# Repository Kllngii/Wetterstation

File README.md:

# Wetterstation

Mit einem WiFi-fähigen Mikrocontroller sollen verschiedene Sensordaten erfasst- und aufbereitet werden. 

Für die WiFi-Anbindung wird ein Raspberry Pi Pico W verwendet, der mit zwei Kernen und einem WLAN/Bluetooth Modul genug Leistung
zur Verfügung stellen kann. 

Die erfassten Daten werden auf einem lokalen (Touch)-Display ausgegeben, durch die WLAN-Fähigkeit könnten die Daten zukünftig auch an eine lokale Datenbank übertragen werden (MySQL/Docker, graphische Aufbereitung mit Grafana o.ä.)

# Sensoren
Folgende Sensoren werden verwendet (das Projekt ist beliebig skalierbar):
## Interne Messgruppe
- BME280 (Temperatur, Luftfeuchtigkeit, Luftdruck)
- MH-Z19C (CO2)
## Externe Messgruppe
- BME280 (Tempertur, Luftfeuchtigkeit, Luftdruck)
- DCF77-Empfänger (Uhrzeit und Wettervorhersage)
    - Der DCF77-Empfänger empfängt das Signal eines Zeitzeichensenders, das neben aktuellen Zeitinformationen eine Wettervorhersage beinhaltet. Diese ist allerdings verschlüsselt. verfügbaren GPIO Pins und Rechenleistung wird die Entschlüsselung auf dem internen Modul vorgenommen. Mit der Nutzung des ESP8266 als Außenmodul ist das ganz sinnvoll, weil der nicht so viele GPIO Pins frei verfügbar hat, ein MSP430 sollte das aber ohne grö0eren Rechenaufwand schaffen. Für die Entschlüsselung der Daten wird ein HKW581 Modul benötigt. 
## Eventuelle Erweiterungen
- DHT22 (Temperatur, Luftfeuchtigkeit)
- PT100/PT1000 (Zwei- oder Vierleitermessung, dazu Konstantstromquelle + rel. hochauflösender ADC (min. 16 bit))
- CCS811 (CO2 und flüchtige organische Verbindungen (TVOC))
- Niederschlagsmessung
- Windgeschwindigkeit und Windrichtung

# Struktur des Repos
- **LaTeX** [Dokumentation des Projekts](#dokumentation)
- **wetterstation-arduinosensor** [Arduino als Sensormodul](#arduino-als-sensormodul)
- **wetterstation-ui/** [Desktop App](#desktop-app)
- **slint-pico/** [Raspberry Pico mit Touchscreen als Interface](#raspberry-pico-mit-touchscreen-als-interface)
- **pcbs/** Hier findet man Schaltpläne und PCBs der Module als [KiCad](https://www.kicad.org) Projekt

# Desktop App

*TODO* Hier müsste man erklären was die Desktop-App ist 

# Dokumentation

Das LaTeX Dokument in diesem Ordner ist die Dokumentation des Projekts.

# Arduino als Sensormodul

Ein kleiner Beispiel-Sketch, der einen Arduino (Uno) benutzt, um die I2C- und Onewire-Sensoren anzusteuern.

# Raspberry Pico mit Touchscreen als Interface 

*TODO* Hier müsste man erklären was die Raspberry-Pi-Pico-App ist

# Aktivität

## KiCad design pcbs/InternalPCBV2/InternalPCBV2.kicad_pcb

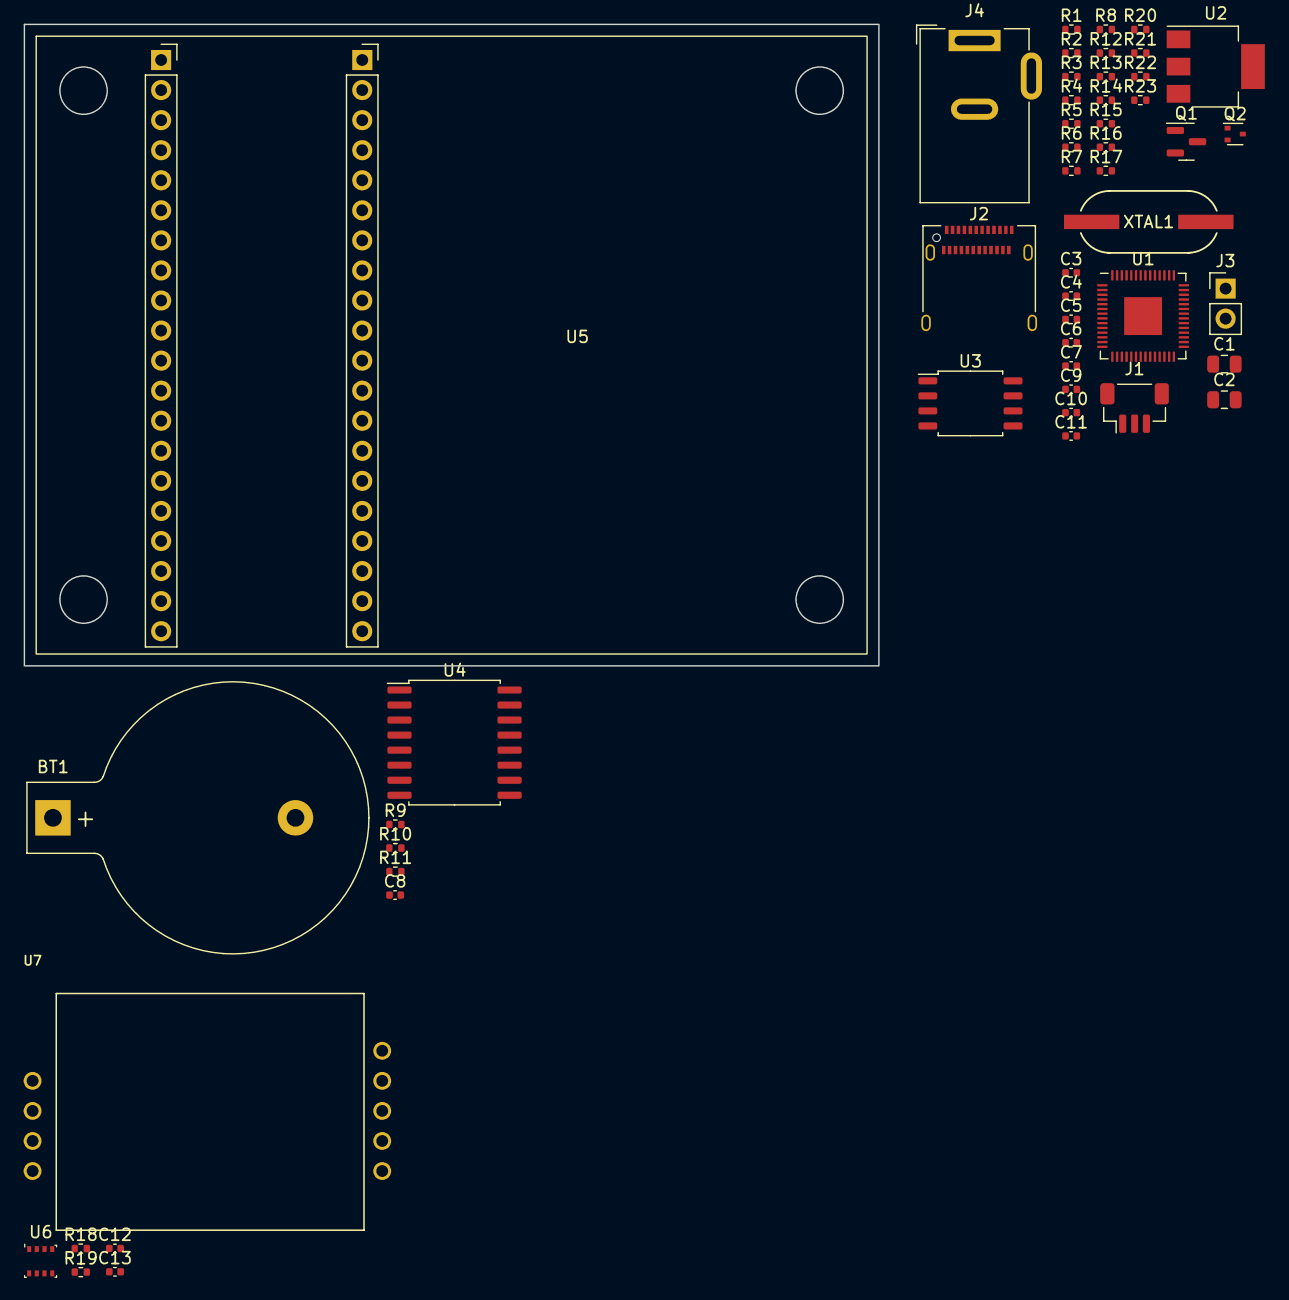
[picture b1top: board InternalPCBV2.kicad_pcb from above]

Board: 2 copper layers, 72.2 x 54.2 mm, 51 parts (0 on the bottom side), 42 nets, no tracks yet.

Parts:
BT1: Battery; BatteryHolder_Keystone_103_1x20mm
C1, C2: 10u; C_0805_2012Metric
C3, C7, C10, C12: 100n; C_0402_1005Metric
C4, C5: 27p; C_0402_1005Metric
C6, C9, C13: 1u; C_0402_1005Metric
C8: 0.1u; C_0402_1005Metric
C11: 1n; C_0402_1005Metric
J1: JST-SH 1x3 SWD Debug; JST_SH_BM03B-SRSS-TB_1x03-1MP_P1.00mm_Vertical
J2: USB_C_Receptacle; USB_C_Receptacle_Amphenol_12401610E4-2A
J3: USB Boot Switch; PinHeader_1x02_P2.54mm_Vertical
J4: 694106301002; BarrelJack_Wuerth_6941xx301002
Q1: DMG2305UX; SOT-23
Q2: DMG1012T; SOT-523
R1, R2: 5.1k; R_0402_1005Metric
R3, R4: 1k; R_0402_1005Metric
R5, R6: 27; R_0402_1005Metric
R7: 100k; R_0402_1005Metric
R8: 200k; R_0402_1005Metric
R9, R10, R11, R18, R19: 10k; R_0402_1005Metric
R12, R13, R14, R15, R16, R17, R20, R21, R22, R23: 0; R_0402_1005Metric
U1: RP2040; QFN-56-1EP_7x7mm_P0.4mm_EP3.2x3.2mm
U2: NCP1117-3.3_SOT223; SOT-223-3_TabPin2
U3: W25Q128JVS; SOIC-8_5.23x5.23mm_P1.27mm
U4: DS3231M; SOIC-16W_7.5x10.3mm_P1.27mm
U5: Pico-ResTouch-LCD-2.8
U6: BME280; Bosch_LGA-8_2.5x2.5mm_P0.65mm_ClockwisePinNumbering
U7: MH-Z19B
XTAL1: ABLS-12.000MHZ-B2-T; XTAL_HC&slash_49US_ABLS_ABR

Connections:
+1V1: C6.1, C7.2, U1.23 (DVDD), U1.45 (VREG_VOUT), U1.50 (DVDD)
+3.3V: C2.1, C3.1, C8.1, C9.1, C10.1, Q2.1 (G), R9.1, R10.1, R11.1, U1.1 (IOVDD), U1.10 (IOVDD), U1.22 (IOVDD), U1.33 (IOVDD), U1.42 (IOVDD), U1.43 (ADC_AVDD), U1.44 (VREG_IN), U1.48 (USB_VDD), U1.49 (IOVDD), U2.2 (VO), U3.8 (VCC), U4.2 (VCC)
+3V3: C12.2, C13.1, R18.1, R19.1, U6.2 (CSB), U6.6 (VDDIO), U6.8 (VDD)
+5V: C1.1, Q1.2 (S), R8.2, U2.3 (VI), U7.VIN
/DEBUG_SC: J1.1, U1.24 (SWCLK)
/DEBUG_SD: J1.3, U1.25 (SWD)
/Display-RTC/I2C0_SCL: R9.2, U4.16 (SCL)
/Display-RTC/I2C0_SDA: R10.2, U4.15 (SDA)
/Display-RTC/RTC_IRQ: R11.2, U4.3 (~INT/SQW)
/FLASH_CLK: U1.52 (QSPI_SCLK), U3.6 (CLK)
/FLASH_CS: R3.2, U1.56 (QSPI_SS), U3.1 (~CS)
/FLASH_SD0: U1.53 (QSPI_SD0), U3.5 (DI(IO0))
/FLASH_SD1: U1.55 (QSPI_SD1), U3.2 (DO(IO1))
/FLASH_SD2: U1.54 (QSPI_SD2), U3.3 (IO2)
/FLASH_SD3: U1.51 (QSPI_SD3), U3.7 (IO3)
/GPIO_0: R22.1, U1.2 (GPIO0)
/GPIO_1: R23.1, U1.3 (GPIO1)
/GPIO_5: R12.1, U1.7 (GPIO5)
/GPIO_18: R13.1, U1.29 (GPIO18)
/GPIO_19: R14.1, U1.30 (GPIO19)
/GPIO_20: R15.1, R20.1
/GPIO_21: R16.1, R21.1
/I2C0_SCL: R21.2, R23.2
/I2C0_SDA: R20.2, R22.2
/Sensors/I2C1_SCL: R18.2, U6.4 (SCK)
/Sensors/I2C1_SDA: R19.2, U6.3 (SDI)
/USB_D+: J2.A6 (D+), J2.B6 (D+), R5.2
/USB_D-: J2.A7 (D-), J2.B7 (D-), R6.1
/VSYS_SENSE: Q2.2 (S), U1.41 (GPIO29_ADC3)
/XIN: C4.2, U1.20 (XIN), XTAL1.1
/XOUT: R4.2, U1.21 (XOUT)
GND: BT1.2 (-), C1.2, C2.2, C3.2, C4.1, C5.1, C6.2, C7.1, C8.2, C9.2, C10.2, C11.1, C12.1, C13.2, J1.2, J2.A1 (GND), J2.A12 (GND), J2.B1 (GND), J2.B12 (GND), J2.S1 (SHIELD), J3.2, J4.2 (GND_1), J4.3 (GND_2), R1.2, R2.2, R7.1, U1.19 (TESTEN), U1.57 (GND), U2.1 (GND), U3.4 (GND), U4.5 (GND), U4.6 (GND), U4.7 (GND), U4.8 (GND), U4.9 (GND), U4.10 (GND), U4.11 (GND), U4.12 (GND), U4.13 (GND), U5.3 (GND), U6.1 (GND), U6.5 (SDO), U6.7 (GND), U7.GND
unnamed: BT1.1 (+), U4.14 (VBAT)
unnamed: C5.2, R4.1, XTAL1.2
unnamed: J2.A5 (CC1), R1.1
unnamed: J2.B5 (CC2), R2.1
unnamed: J3.1, R3.1
unnamed: J4.1 (POWER), Q1.3 (D)
unnamed: C11.2, Q2.3 (D), R7.2, R8.1
unnamed: R6.2, U1.46 (USB_DM)
unnamed: R5.1, U1.47 (USB_DP)
VBUS: J2.A4 (VBUS), J2.A9 (VBUS), J2.B4 (VBUS), J2.B9 (VBUS), Q1.1 (G)

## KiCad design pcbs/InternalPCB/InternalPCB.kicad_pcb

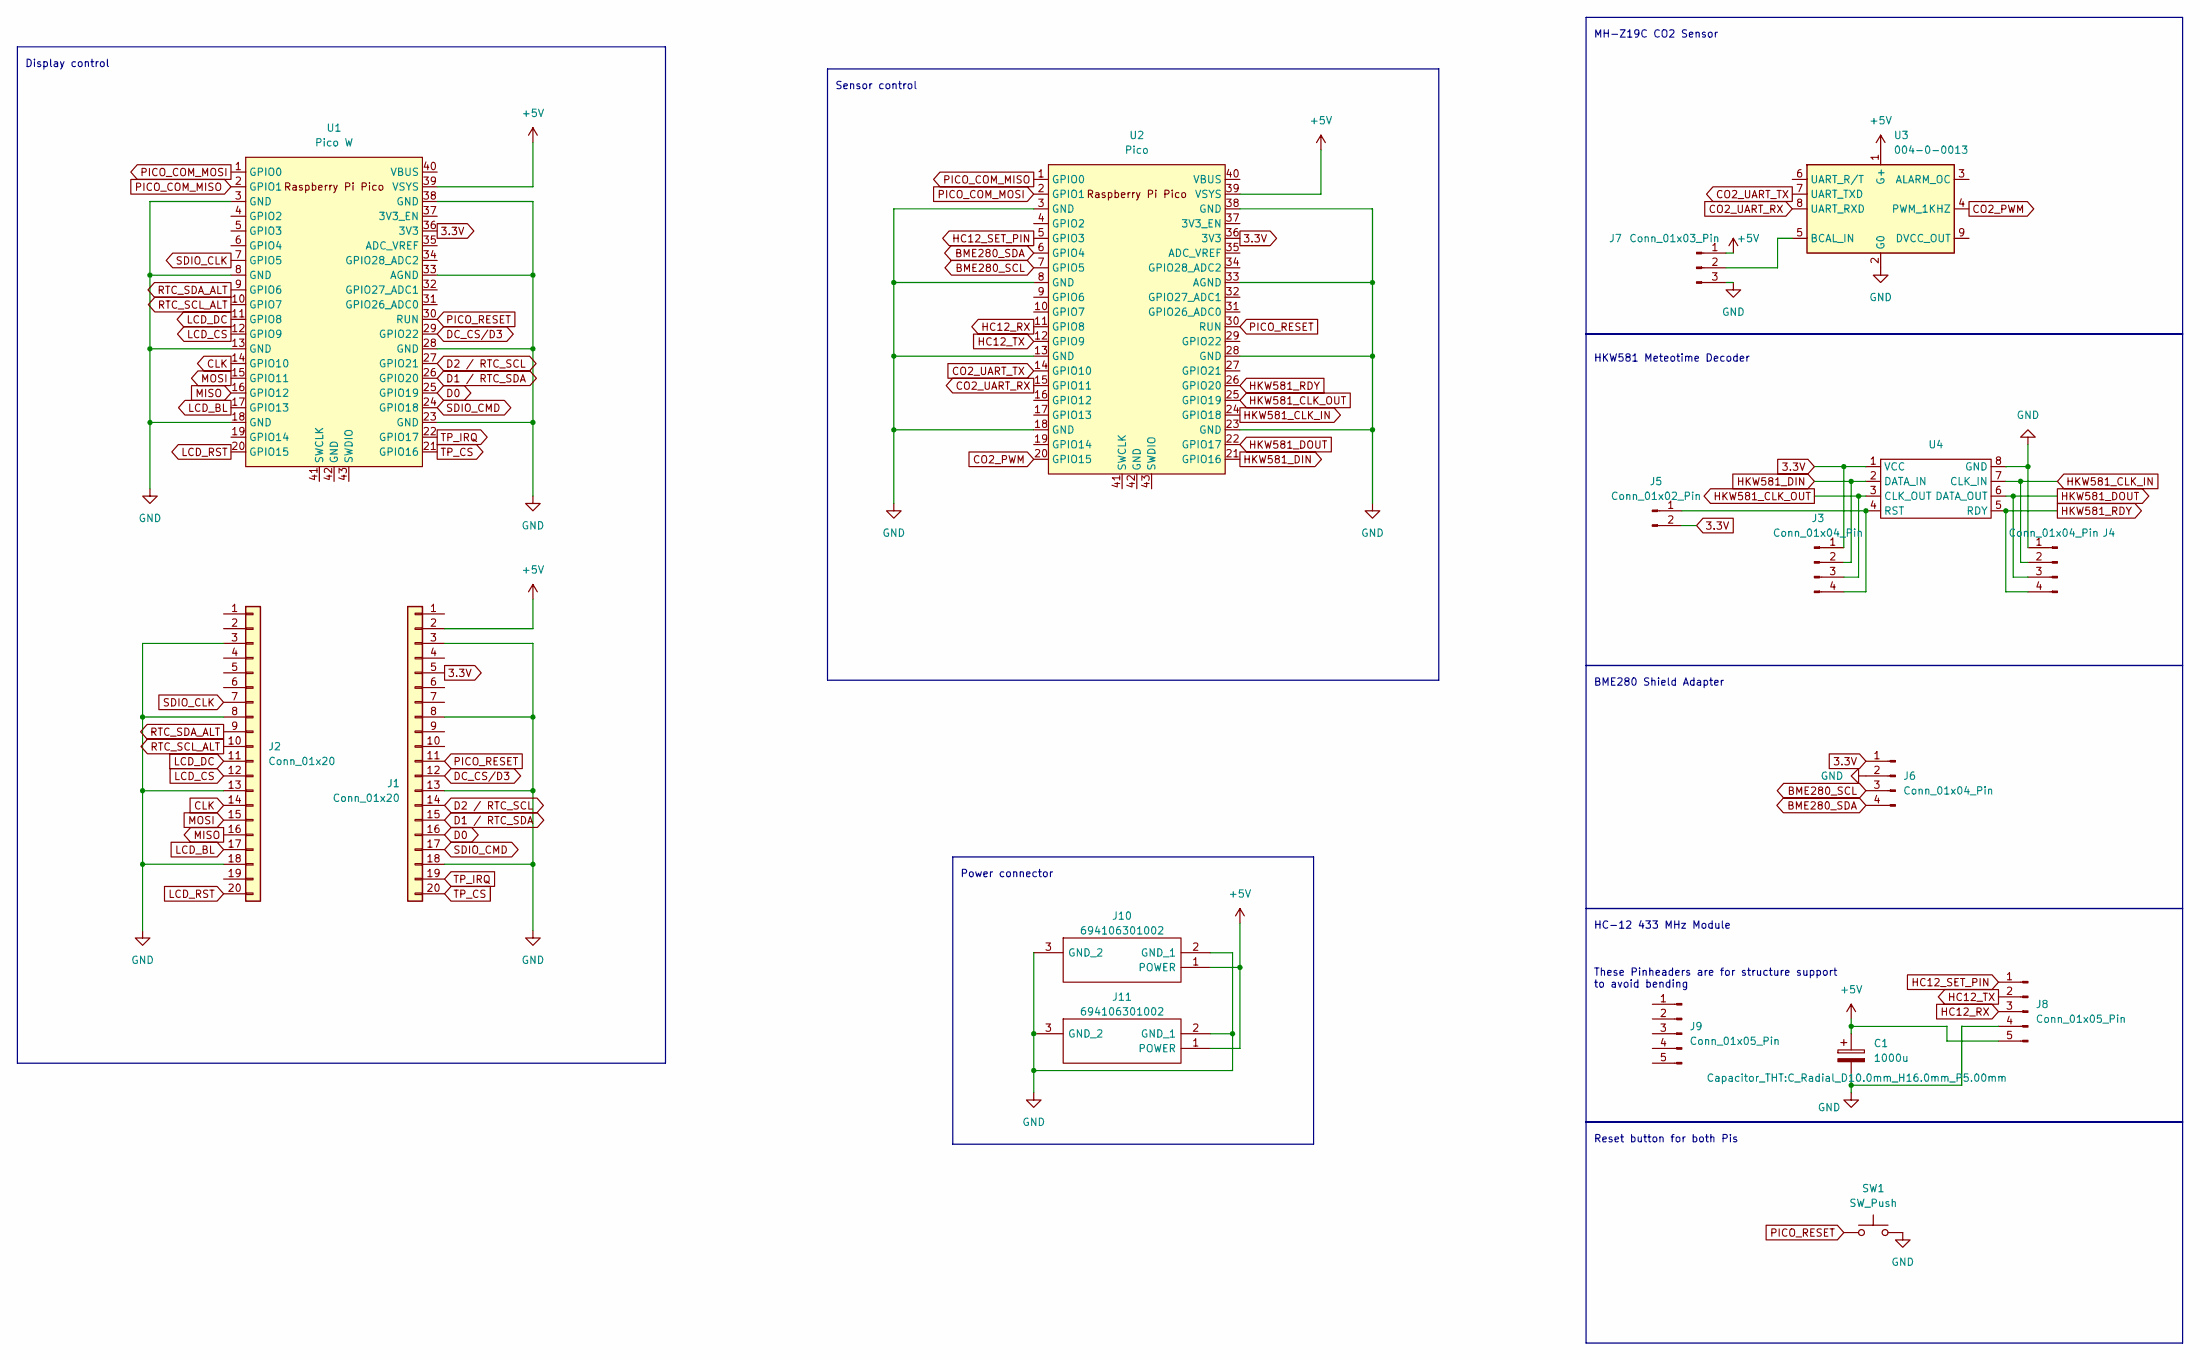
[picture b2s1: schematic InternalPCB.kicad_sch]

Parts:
C1: 1000u; C_Radial_D10.0mm_H16.0mm_P5.00mm
J1, J2: Conn_01x20; PinHeader_1x20_P2.54mm_Vertical
J3, J4, J6: Conn_01x04_Pin; PinHeader_1x04_P2.54mm_Vertical
J5: Conn_01x02_Pin; PinHeader_1x02_P2.54mm_Vertical
J7: Conn_01x03_Pin; PinHeader_1x03_P2.54mm_Vertical
J8, J9: Conn_01x05_Pin; PinHeader_1x05_P2.54mm_Vertical
J10, J11: 694106301002; 694106301002_1; Manufacturer_Part_Number 694106301002; Mouser Part Number 710-694106301002
SW1: SW_Push; SW_PUSH_6mm
U1: Pico W; RPi_Pico_SMD_TH
U2: Pico; RPi_Pico_SMD_TH
U3: 004-0-0013; Senseair_S8_Down
U4: MSOP-8_3x3mm_P0.65mm

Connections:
3.3V: J1.5, J3.1, J5.2, J6.1, U1.36 (3V3), U2.36 (3V3), U4.1 (VCC)
+5V: C1.1, J1.2, J7.1, J8.5, J10.1 (POWER), J11.1 (POWER), U1.39 (VSYS), U2.39 (VSYS), U3.1 (G+)
BME280_SCL: J6.3, U2.7 (GPIO5)
BME280_SDA: J6.4, U2.6 (GPIO4)
CLK: J2.14, U1.14 (GPIO10)
CO2_PWM: U2.20 (GPIO15), U3.4 (PWM_1KHZ)
CO2_UART_RX: U2.15 (GPIO11), U3.8 (UART_RXD)
CO2_UART_TX: U2.14 (GPIO10), U3.7 (UART_TXD)
D0: J1.16, U1.25 (GPIO19)
D1 / RTC_SDA: J1.15, U1.26 (GPIO20)
D2 / RTC_SCL: J1.14, U1.27 (GPIO21)
DC_CS/D3: J1.12, U1.29 (GPIO22)
GND: C1.2, J1.3, J1.8, J1.13, J1.18, J2.3, J2.8, J2.13, J2.18, J4.1, J6.2, J7.3, J8.4, J10.2 (GND_1), J10.3 (GND_2), J11.2 (GND_1), J11.3 (GND_2), SW1.2, U1.3 (GND), U1.8 (GND), U1.13 (GND), U1.18 (GND), U1.23 (GND), U1.28 (GND), U1.33 (AGND), U1.38 (GND), U2.3 (GND), U2.8 (GND), U2.13 (GND), U2.18 (GND), U2.23 (GND), U2.28 (GND), U2.33 (AGND), U2.38 (GND), U3.2 (G0), U4.8 (GND)
HC12_RX: J8.3, U2.11 (GPIO8)
HC12_SET_PIN: J8.1, U2.5 (GPIO3)
HC12_TX: J8.2, U2.12 (GPIO9)
HKW581_CLK_IN: J4.2, U2.24 (GPIO18), U4.7 (CLK_IN)
HKW581_CLK_OUT: J3.3, U2.25 (GPIO19), U4.3 (CLK_OUT)
HKW581_DIN: J3.2, U2.21 (GPIO16), U4.2 (DATA_IN)
HKW581_DOUT: J4.3, U2.22 (GPIO17), U4.6 (DATA_OUT)
HKW581_RDY: J4.4, U2.26 (GPIO20), U4.5 (RDY)
LCD_BL: J2.17, U1.17 (GPIO13)
LCD_CS: J2.12, U1.12 (GPIO9)
LCD_DC: J2.11, U1.11 (GPIO8)
LCD_RST: J2.20, U1.20 (GPIO15)
MISO: J2.16, U1.16 (GPIO12)
MOSI: J2.15, U1.15 (GPIO11)
unnamed: J3.4, J5.1, U4.4 (RST)
unnamed: J7.2, U3.5 (BCAL_IN)
PICO_COM_MISO: U1.2 (GPIO1), U2.1 (GPIO0)
PICO_COM_MOSI: U1.1 (GPIO0), U2.2 (GPIO1)
PICO_RESET: J1.11, SW1.1, U1.30 (RUN), U2.30 (RUN)
RTC_SCL_ALT: J2.10, U1.10 (GPIO7)
RTC_SDA_ALT: J2.9, U1.9 (GPIO6)
SDIO_CLK: J2.7, U1.7 (GPIO5)
SDIO_CMD: J1.17, U1.24 (GPIO18)
TP_CS: J1.20, U1.21 (GPIO16)
TP_IRQ: J1.19, U1.22 (GPIO17)

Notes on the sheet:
HKW581 Meteotime Decoder
Display control
BME280 Shield Adapter
HC-12 433 MHz Module
Power connector
Sensor control
Reset button for both Pis
These Pinheaders are for structure support to avoid bending
MH-Z19C CO2 Sensor

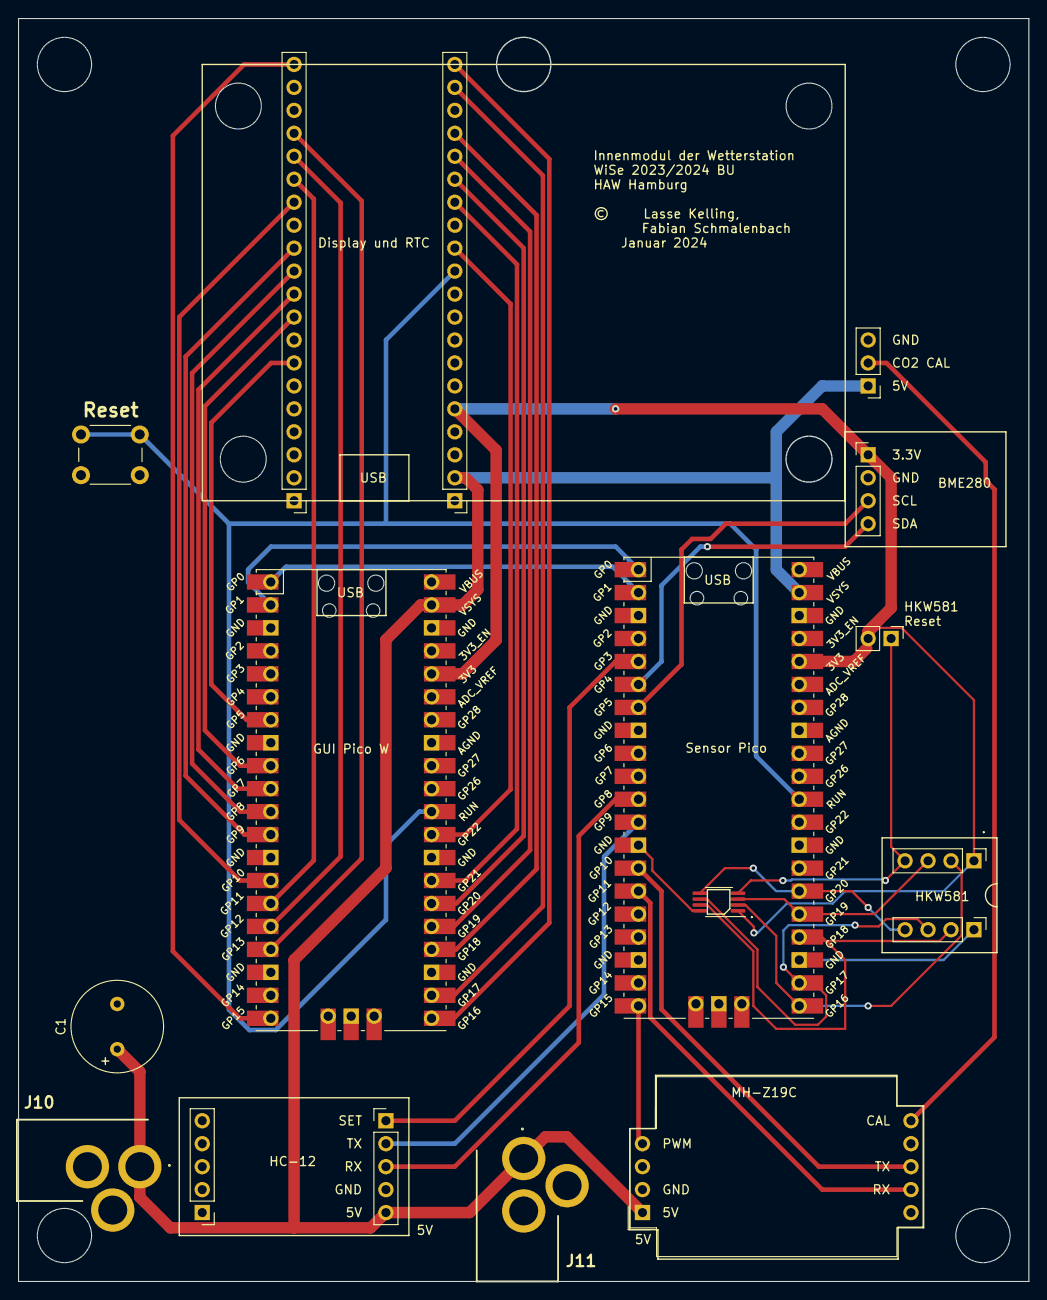
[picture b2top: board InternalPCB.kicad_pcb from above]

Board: 2 copper layers, 111.8 x 139.7 mm, 17 parts (0 on the bottom side), 38 nets.

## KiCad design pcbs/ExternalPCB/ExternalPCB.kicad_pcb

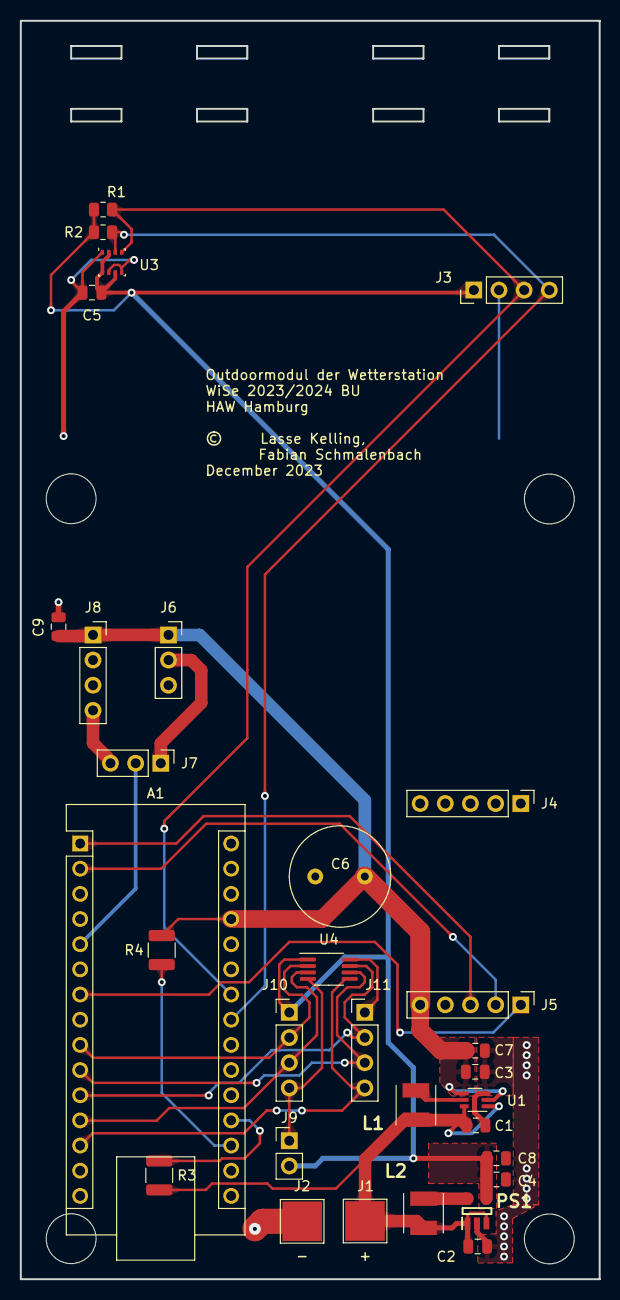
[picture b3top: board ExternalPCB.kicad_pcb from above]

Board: 2 copper layers, 58.4 x 127.0 mm, 31 parts (0 on the bottom side), 22 nets.

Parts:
A1: Arduino_Nano_Every; Arduino_Nano
C1, C2: 22u; C_0805_2012Metric
C3, C4: 10u; C_0805_2012Metric
C5, C7, C8, C9: 100n; C_0805_2012Metric
C6: 1000u; C_Radial_D10.0mm_H16.0mm_P5.00mm
J1: Bat +; TestPoint_Pad_4.0x4.0mm
J2: Bat -; TestPoint_Pad_4.0x4.0mm
J3, J10, J11: Conn_01x04_Pin; PinHeader_1x04_P2.54mm_Vertical
J4, J5: Conn_01x05_Pin; PinHeader_1x05_P2.54mm_Vertical
J6: Conn_01x03_Pin; PinSocket_1x03_P2.54mm_Vertical
J7: Conn_01x03_Pin; PinHeader_1x03_P2.54mm_Vertical
J8: Conn_01x04_Pin; PinSocket_1x04_P2.54mm_Vertical
J9: Conn_01x02_Pin; PinHeader_1x02_P2.54mm_Vertical
L1, L2: LQH44PN4R7MJ0L; LQH44PN100MJ0L
PS1: TPS61097A-33DBVR; SOT95P280X145-5N
R1, R2: 4.7k; R_0805_2012Metric
R3, R4: 0; R_1210_3225Metric
U1: TPS61222DCK; Texas_R-PDSO-G6
U3: BME280; Bosch_LGA-8_2.5x2.5mm_P0.65mm_ClockwisePinNumbering
U4: MSOP-8_3x3mm_P0.65mm

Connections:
+3.3V: C4.1, C5.1, C8.1, J3.1, J9.2, J10.1, PS1.4 (VOUT), R1.1, R2.1, U3.2 (CSB), U3.6 (VDDIO), U3.8 (VDD), U4.1 (VCC)
+5V: A1.27 (+5V), C3.1, C6.1, C7.1, C9.1, J5.5, J6.1, J8.1, R4.2, U1.2 (FB), U1.4 (VOUT)
+BATT: C1.1, C2.1, J1.1, L1.1, L2.1, PS1.1 (VIN), PS1.3 (EN), R3.2, U1.1 (VIN), U1.6 (EN)
-BATT: A1.4 (GND), A1.29 (GND), C1.2, C2.2, C3.2, C4.2, C5.2, C6.2, C7.2, C8.2, C9.2, J2.1, J3.2, J5.4, J6.3, J8.2, J8.3, J11.1, PS1.2 (GND), U1.3 (GND), U3.1 (GND), U3.5 (SDO), U3.7 (GND), U4.8 (GND)
BATTERY_VOLTAGE: A1.19 (A0), R3.1
DCF_DATA: A1.5 (D2), J7.2
HC12_RX: A1.1 (TX1), J5.3
HC12_SET_PIN: A1.7 (D4), J5.1
HC12_TX: A1.2 (RX1), J5.2
HKW581_CLK_IN: A1.11 (D8), J11.2, U4.7 (CLK_IN)
HKW581_CLK_OUT: A1.12 (D9), J10.3, U4.3 (CLK_OUT)
HKW581_DATA_IN: A1.9 (D6), J10.2, U4.2 (DATA_IN)
HKW581_DATA_OUT: A1.10 (D7), J11.3, U4.6 (DATA_OUT)
HKW581_RDY: A1.13 (D10), J11.4, U4.5 (RDY)
I2C_SCL: A1.24 (SCL/A5), J3.3, R1.2, U3.4 (SCK)
I2C_SDA: A1.23 (SDA/A4), J3.4, R2.2, U3.3 (SDI)
unnamed: J6.2, J7.1
unnamed: J7.3, J8.4
unnamed: J9.1, J10.4, U4.4 (RST)
unnamed: L2.2, PS1.5 (L)
unnamed: L1.2, U1.5 (L)
REF_VOLTAGE: A1.18 (AREF), R4.1

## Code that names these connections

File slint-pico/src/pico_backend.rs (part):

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};

pub type TargetPixel = Rgb565Pixel;
type IrqPin = gpio::Pin<gpio::bank0::Gpio17, gpio::FunctionSio<gpio::SioInput>, gpio::PullUp>;
type SpiPins = (
    gpio::Pin<gpio::bank0::Gpio11, gpio::FunctionSpi, gpio::PullDown>,
    gpio::Pin<gpio::bank0::Gpio12, gpio::FunctionSpi, gpio::PullDown>,
    gpio::Pin<gpio::bank0::Gpio10, gpio::FunctionSpi, gpio::PullDown>,
);
type UartPins = (
    gpio::Pin<gpio::bank0::Gpio0, gpio::FunctionUart, gpio::PullNone>,
    gpio::Pin<gpio::bank0::Gpio1, gpio::FunctionUart, gpio::PullNone>,
);
type I2CPins = (
    gpio::Pin<gpio::bank0::Gpio20, gpio::FunctionI2C, gpio::PullUp>,
    gpio::Pin<gpio::bank0::Gpio21, gpio::FunctionI2C, gpio::PullUp>,
);
type EnabledSpi = hal::Spi<hal::spi::Enabled, pac::SPI1, SpiPins, 8>;
type EnabledUart = hal::uart::UartPeripheral<hal::uart::Enabled, pac::UART0, UartPins>;
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
    // *** Pins und benötigte Schnittstellen konfigurieren ***

    let rst = pins.gpio15.into_push_pull_output(); //Reset
    let bl = pins.gpio13.into_push_pull_output(); //Backlight

    let dc = pins.gpio8.into_push_pull_output(); //Data/Command
    let cs = pins.gpio9.into_push_pull_output(); //Display-Chipselect

    let spi_sclk = pins.gpio10.into_function::<gpio::FunctionSpi>();
    let spi_mosi = pins.gpio11.into_function::<gpio::FunctionSpi>();
    let spi_miso = pins.gpio12.into_function::<gpio::FunctionSpi>();

    let spi = hal::Spi::new(pac.SPI1, (spi_mosi, spi_miso, spi_sclk));
    let spi = spi.init(
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    //TODO Funktion testen & Backlight bei Inaktivität ausschalten
    display.set_backlight(BacklightState::On, &mut delay).unwrap();

    let touch_irq = pins.gpio17.into_pull_up_input();
    touch_irq.set_interrupt_enabled(GpioInterrupt::LevelLow, true);

    cortex_m::interrupt::free(|cs| {
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    });
    let touch = XPT2046::new(
        &IRQ_PIN,
        pins.gpio16.into_push_pull_output(),
        SharedSpiWithFreq { mutex: spi_mutex, freq: xpt2046::SPI_FREQ },
        DISPLAY_ORIENTATION,
    )
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        stolen_pin: (dc_copy, cs_copy),
    };

    let _i2c_sda: gpio::Pin<_, gpio::FunctionI2C, gpio::PullUp> = pins.gpio20.reconfigure();
    let _i2c_scl: gpio::Pin<_, gpio::FunctionI2C, gpio::PullUp> = pins.gpio21.reconfigure();

    let i2c = I2C::new_controller(
        pac.I2C0,
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    });

    let uart_pins = (
        pins.gpio0.reconfigure::<gpio::FunctionUart, gpio::PullNone>(),
        pins.gpio1.reconfigure::<gpio::FunctionUart, gpio::PullNone>(),
    );

    let mut uart = hal::uart::UartPeripheral::new(pac.UART0, uart_pins, &mut pac.RESETS)
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
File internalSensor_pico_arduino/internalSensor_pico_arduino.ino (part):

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#define UART0_TX        0
#define UART0_RX        1

#define HC12_TX         8
#define HC12_RX         9
#define HC12_SET_PIN    3

#define CO2_PWM_PIN     15

#define BME_SEND_FREQUENCY_MILLIS   30000
#define CO2_SEND_FREQUENCY_MILLIS   15000
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#define READ_TIMEOUT    100 // Timeout value after which the uC stops polling for Serial data from HC12

Adafruit_BME280 bme;    // BME280, read by core0
CO2 co2(CO2_PWM_PIN, MHZ19C, CO2::RANGE_5K);
CO2SendBuf co2Buffer = {'C','O','2','.'};
BMESendBuf iBmeBuffer = {'I','B','M','E'};

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        Serial.println("Found bme.");
    }

    pinMode(HC12_SET_PIN, OUTPUT);

    // Set Baudrate to 9600
    delay(100);
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    Serial.println(hcAnswerArray);

    // Disable Setting Mode in HC-12
    pinMode(HC12_SET_PIN, INPUT);
}

void setup1()
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
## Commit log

2023-10-24 Initialpush
2023-10-24 so konfiguriert man eine I2C-Schnittstelle per TivaC, theoretisch
2023-10-25 kleines Projekt für den UI-Teil angelegt
2023-10-25 die in-Properties können jetzt aus rust angesprochen werden
2023-10-27 Projekt neu geordnet
2023-10-27 kleiner Testsketch, um Beispielwerte zu empfangen
2023-10-27 Werte aktualisieren sich jetzt in der GUI
2023-10-27 kleiner Ringbuffer Test
2023-10-27 Aufgaben ergänzt
2023-10-30 Added LaTeX Document
2023-11-04 kleine Anpassungen, um BME280 und CCS811 Sensordaten abzufragen
2023-11-04 TI µC wird nicht verwendet, Projekt entfällt
2023-11-05 animierter Graph + Vorbereitung für neue Messdaten
2023-11-05 Ungetesteter Code für ein Touchscreen an einem Raspberry Pico
2023-11-05 neues Farbschema für TopWidgets + CO2 PieChart ergänzt
2023-11-05 Neues Farbschema jetzt überall angewendet
2023-11-05 Da fehlte noch das neue Farbschema...
2023-11-06 Neue UI Sachen
2023-11-09 Fade-Effekte
2023-11-13 neuen tollen Logger eingebunden
2023-11-14 Added DCF77 example
2023-11-19 Added arduino libs
2023-11-19 Added readme
2023-11-19 Moved dcf77 test
2023-11-19 Added 433MHz testprogram
2023-11-19 Fixed minor but ugly formatting mistake
2023-11-19 Added Time library
2023-11-19 created ino-project for meteotime decoder
2023-11-20 ganz tolles Testprojekt
2023-11-20 Initialpush Slint-pico
2023-11-20 hübsche UI
2023-11-20 noch hübschere UI
2023-11-25 Added BME280 transmit
2023-11-25 Updated tex structure
2023-11-25 Bisschen in der Ausarbeitung tüddeln
2023-11-26 rp-pico BoardSupport-Package von v0.5 auf v0.8
2023-11-27 idea Files für den RustRover
2023-11-27 Neue rust Version
2023-11-29 Jetzt mit Touch und DMA
2023-11-29 Co2 testprogram. Not working
2023-11-29 Vorbereitungen für bessere UI
2023-11-29 UART Beispielimplementierung (TX)
2023-11-29 Defined struct
2023-11-29 UART Beispielimplementierung (TX & RX)
2023-12-01 Implemented external sensor device based on esp
2023-12-02 Copied dfc77 library to arduinoproject to modify it
2023-12-02 Implemented encoded meteodata transmission
2023-12-02 Restructured arduino programs
2023-12-02 Added structs and basic CO2 example
2023-12-02 Removed irrelevant file
2023-12-02 Changed CO2 library for faster readings
2023-12-02 Moved structs and unions in separate files
2023-12-02 Removed irrelevant libs
2023-12-02 Updated gitignore
2023-12-02 Added datatype for co2 sensor
2023-12-02 Fixed bug and changed transmission mode
2023-12-02 Testprogram with all sensors
2023-12-03 Die DMA + Touch Variante kann jetzt ebenfalls UART und I2C
2023-12-04 Aufgeräumt & kommentiert
2023-12-04 Slint Debug-Nachrichten werden jetzt auf debug-Prio verschickt
2023-12-04 unnötige Imports entfernt
2023-12-04 Neuer Trait für Slice -> Number Umwandlungen
2023-12-04 Interner BME und CO2 Sensor funktionieren jetzt
2023-12-04 Zeitstempel auslesen funktioniert jetzt
2023-12-04 Working example with transmission
2023-12-04 Removed unused structs
2023-12-04 Added Meteo packet discovery
2023-12-06 Kleiner Hotfix am Morgen vertreibt Kummer und Sorgen
2023-12-06 Weil es so schön war gleich noch einer
2023-12-10 Rebase mit neuem Demoprojekt
2023-12-10 Changed meteo datatype for better decodation
2023-12-10 Added meteo packet order check
2023-12-10 Accidentally removed lines
2023-12-10 Added example programs for meteodecoder
2023-12-10 Created project for msp
2023-12-10 Added meteo decoder and changed to arduino nano
2023-12-10 panisches Zwischenspeichern, weil es erstmal läuft
2023-12-11 altes Projekt entfernt
2023-12-11 alles außer CO2 wird jetzt angezeigt
2023-12-11 Changed power settings
2023-12-11 Wetterdaten parsen ist jetzt nicht mehr völlig unmöglich
2023-12-12 Created Pico on Arduino IDE
2023-12-14 aufgeräumt
2023-12-14 Bei LandscapeSwapped wird Touch mit invertiert
    Die Bildschirm-Orientierung kann somit wieder auf LandscapeSwapped gesetzt werden.
2023-12-15 Die Wochentage auf der Wetterseite werden jetzt gesetzt
2023-12-15 Copied and Renamed CO2 Interface
2023-12-17 Added not quite working bme280 library
2023-12-17 Removed submodule
2023-12-17 UNTESTED! Added internal Sensorprogram for pi pico
2023-12-17 Neue Dokustruktur
2023-12-17 Beschreibung + Anforderungen
2023-12-17 Format
2023-12-17 Systemübersicht
2023-12-17 Included drawio
2023-12-17 Sensoren
2023-12-17 DCF77
2023-12-17 LASSE DEINE MATNR FEHLT NOCH
2023-12-17 Meteo
2023-12-17 Funkstrecke
2023-12-17 Datenpakete
2023-12-17 Renamed latex datatype file
2023-12-17 Gitignore vergessen...
2023-12-17 Modul extern
2023-12-17 Innenmodul + Projektstand
2023-12-17 Kleines Uppsala korrigiert
2023-12-17 Fixed meteo bugs
2023-12-17 Renamed datatypes
2023-12-18 MATR NR FEHLT NICHT MEHR
2023-12-18 Meteotime Decoder erweitert
2023-12-18 Absatz zur GUI hinzugefügt
2023-12-18 Fixed bugs
2023-12-18 Switched from SoftwareSerial to native UART
2023-12-18 Deactivated WiFi
2023-12-18 Disabled serial reading
2023-12-18 Updated Datatypes
2023-12-19 Meteotime in eigenes Modul ausgelagert
2023-12-20 CO2 läuft
2023-12-23 Added testprogram for HC12
2023-12-23 Switched back to SoftwareSerial
2023-12-23 Send error message when no BME Found
2023-12-23 Added checksum calculation
2023-12-23 Removed sending bme error message
2023-12-24 Added retransmission
2023-12-24 Added CRC check on internal module
2023-12-25 Fixed packing issue and added packet check and retransmission
2023-12-25 Fixed bug
2023-12-25 Enabled DCF Debugging and fixed pressure scaling
2023-12-25 Updated HC12-reading structure
2023-12-26 Fixed bugs at meteotransmission
2023-12-26 Incremented 433 Mhz Power
2023-12-26 Tidy up
2023-12-26 Removed MSP program from main branch
2023-12-26 Added comments
2023-12-26 Changed checksum calculation
2023-12-26 Added submodules for reference
2023-12-26 Nochmal kurz dazu geschrieben, wer den Buchstabenhaufen verzapft hat
2023-12-26 Nochmal kurz den Auto für den Müll hinzugefügt
2023-12-27 DCF-Filter test
2023-12-28 Internal PCB schematic
2023-12-28 Nix wildes
2023-12-28 Moved Meteodecoder to external uC
2023-12-29 Higher chance of meteodata + added filter
2023-12-29 Call-by-reference kriege ich nie im ersten Anlauf hin...
2023-12-29 Disabled logging
2023-12-29 Added decodervalue check
2023-12-29 Removed old external program
2023-12-29 Added weekday and fixed wrong second
2023-12-29 Fixed typo
2023-12-29 Kleiner DCF77 Encoder für den RPico
2023-12-29 Meteotime Decoder weitergebaut
2023-12-29 PCB for external module
2023-12-30 Added teardrops
2023-12-30 One more try reading the CO2 sensor via UART
2023-12-30 DNP BME280 IC
2023-12-30 Will net
2024-01-03 Innenmodul erstes funktionales PCB
2024-01-03 DCF77-Pico weiter
2024-01-03 3,3V für RTC ausgeführt
2024-01-04 PCB Innenmodul verbessert
    - Löcher für Displaymontage
    - 2. Stromanschluss für Wandmontage
    - M3 Löcher für Gehäuse und Wandmontage
    - Beschriftung angepasst
2024-01-04 Elko footprint getauscht
2024-01-04 Bisschen DRC dies das
2024-01-04 JLCPCB hatte ein paar Teile nicht...
2024-01-04 Gerber files
2024-01-11 Neues Wettericon "Foggy" hinzugefügt
2024-01-19 Ein paar Kommentare hinzugefügt
2024-01-20 Send DCF Time to picow without weekday
2024-01-20 Enabled Meteofilter and addes Summertime offset
2024-01-21 Bugfix
2024-01-22 Bisschen aufgehübscht
2024-01-22 Aufräumen
2024-01-22 Doku :)
2024-01-23 RTC wird jetzt über DCF77 Pakete gesetzt
2024-01-23 Neue Wettericons hinzugefügt
2024-01-23 Zeit kann jetzt beim Flashen einmalig gesetzt werden
2024-01-23 Chenged bme transmission frequency
2024-01-23 MeteoSim kann Meteotime Pakete und dazugehörige Zeitstempel imitieren
2024-01-23 Der Meteotime-Decoder speichert jetzt alle Teile der 4 Tage Vorhersage
2024-01-23 Optimized DCF Filter
2024-01-23 kleiner Bugfix am Meteotime Code
2024-01-23 Mehr doku
2024-01-23 Die Uhrzeit sieht jetzt hübsch aus
2024-01-23 Ablaufdiagramme eingefügt
2024-01-23 Noch mehr doku
2024-01-23 Ausarbeitung Zwischenstand
2024-01-23 alte Debug-Ausgaben entfernt
2024-01-23 Graphik ausgetauscht
2024-01-24 Ausarbeitung aktualisiert
2024-01-24 Link zum Repo eingefügt
2024-01-24 HKW durchgehend rödeln lassen
2024-01-24 Send weekday
2024-01-24 Wochentag Fix
2024-01-28 RP2040 ist jetzt direkt auf PCB
2024-01-30 Neue Datei für Display & RTC Chip(s)
2024-01-31 Symbol und Footprint für Display
    Achtung: Pinleiste und Rahmen sind noch nicht zueinander ausgerichtet!!!
2024-01-31 Ein bisschen weitergespielt
2024-01-31 Update fp-info-cache
2024-01-31 Vorbereitungen fürs Backlight nachts ausschalten
2024-02-04 Neuer Footprint für MH-Z19B/C CO2 Sensor
2024-02-05 Der RTC Code verwendet jetzt die DS323x Lib
    Alles sollte wie bisher laufen, außer das Setzen der Zeit über das DCF Signal

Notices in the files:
README.md:
MIT License
Apache-2.0 License
pcbs/ExternalPCB/ExternalPCB.kicad_pcb:
© 	Lasse Kelling,
Fabian Schmalenbach
